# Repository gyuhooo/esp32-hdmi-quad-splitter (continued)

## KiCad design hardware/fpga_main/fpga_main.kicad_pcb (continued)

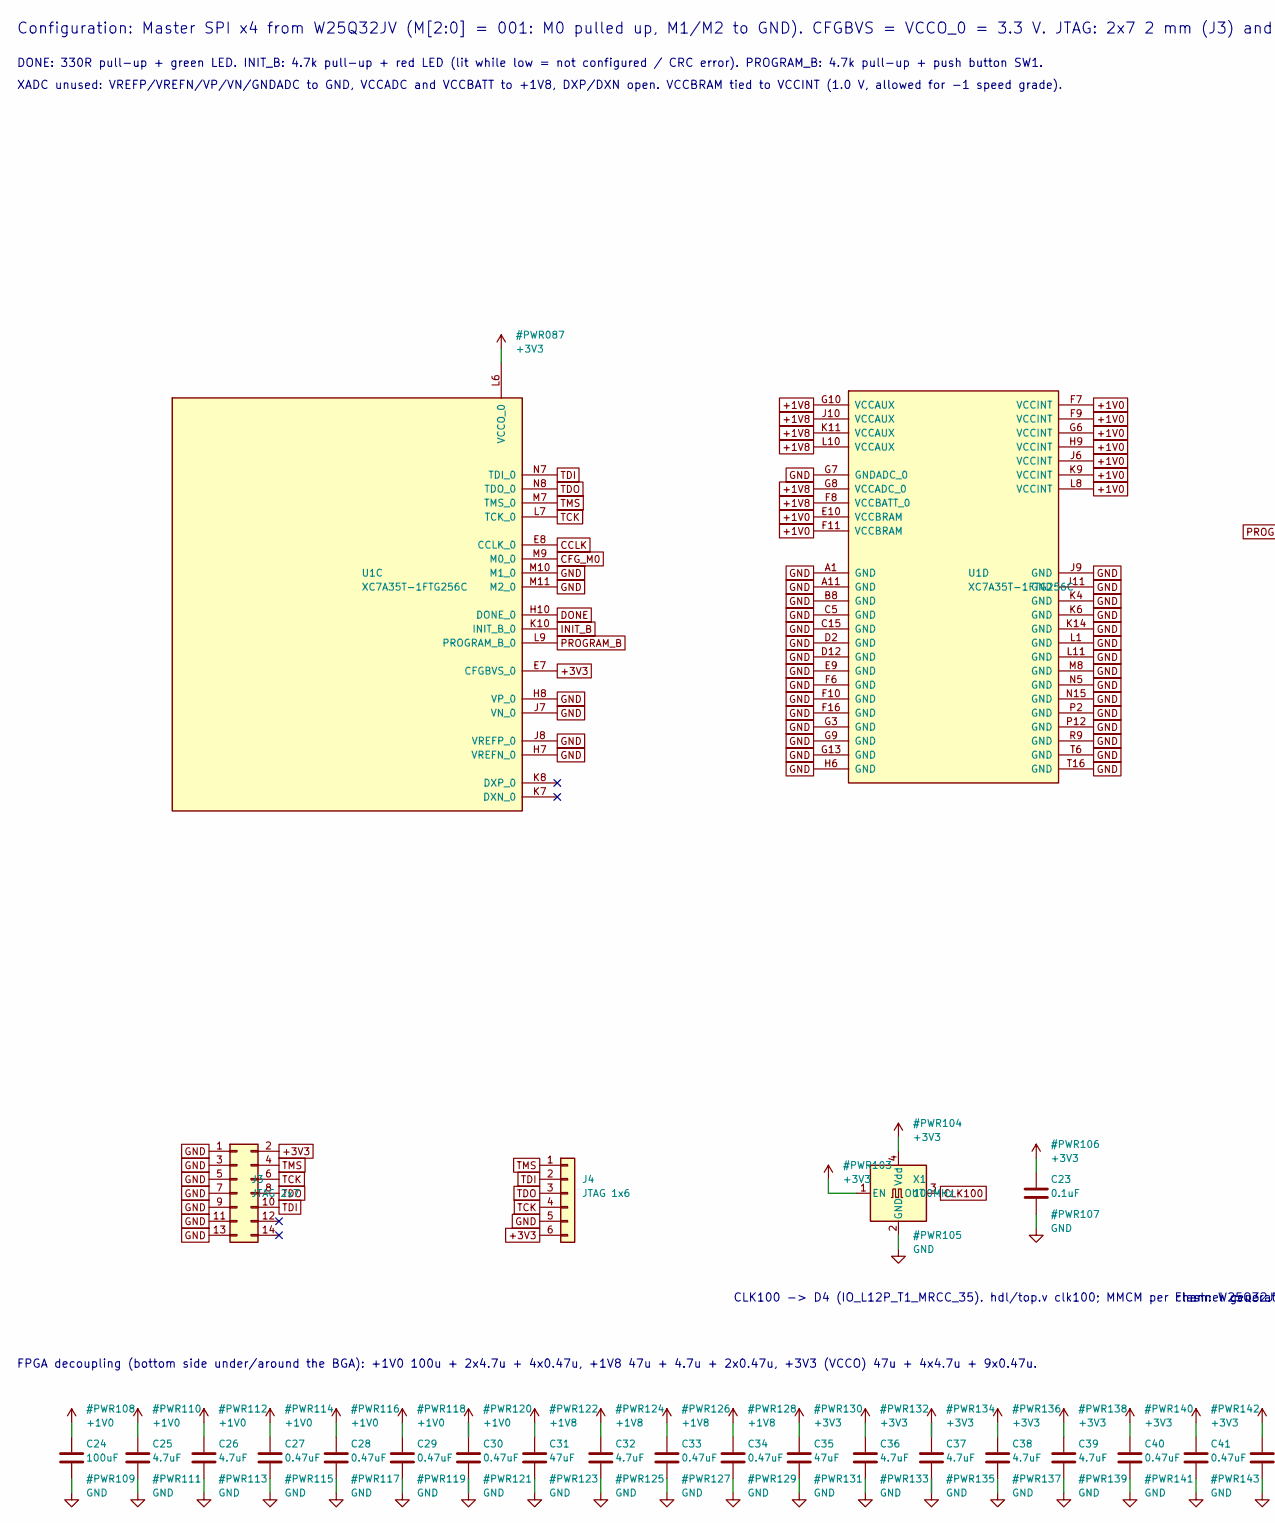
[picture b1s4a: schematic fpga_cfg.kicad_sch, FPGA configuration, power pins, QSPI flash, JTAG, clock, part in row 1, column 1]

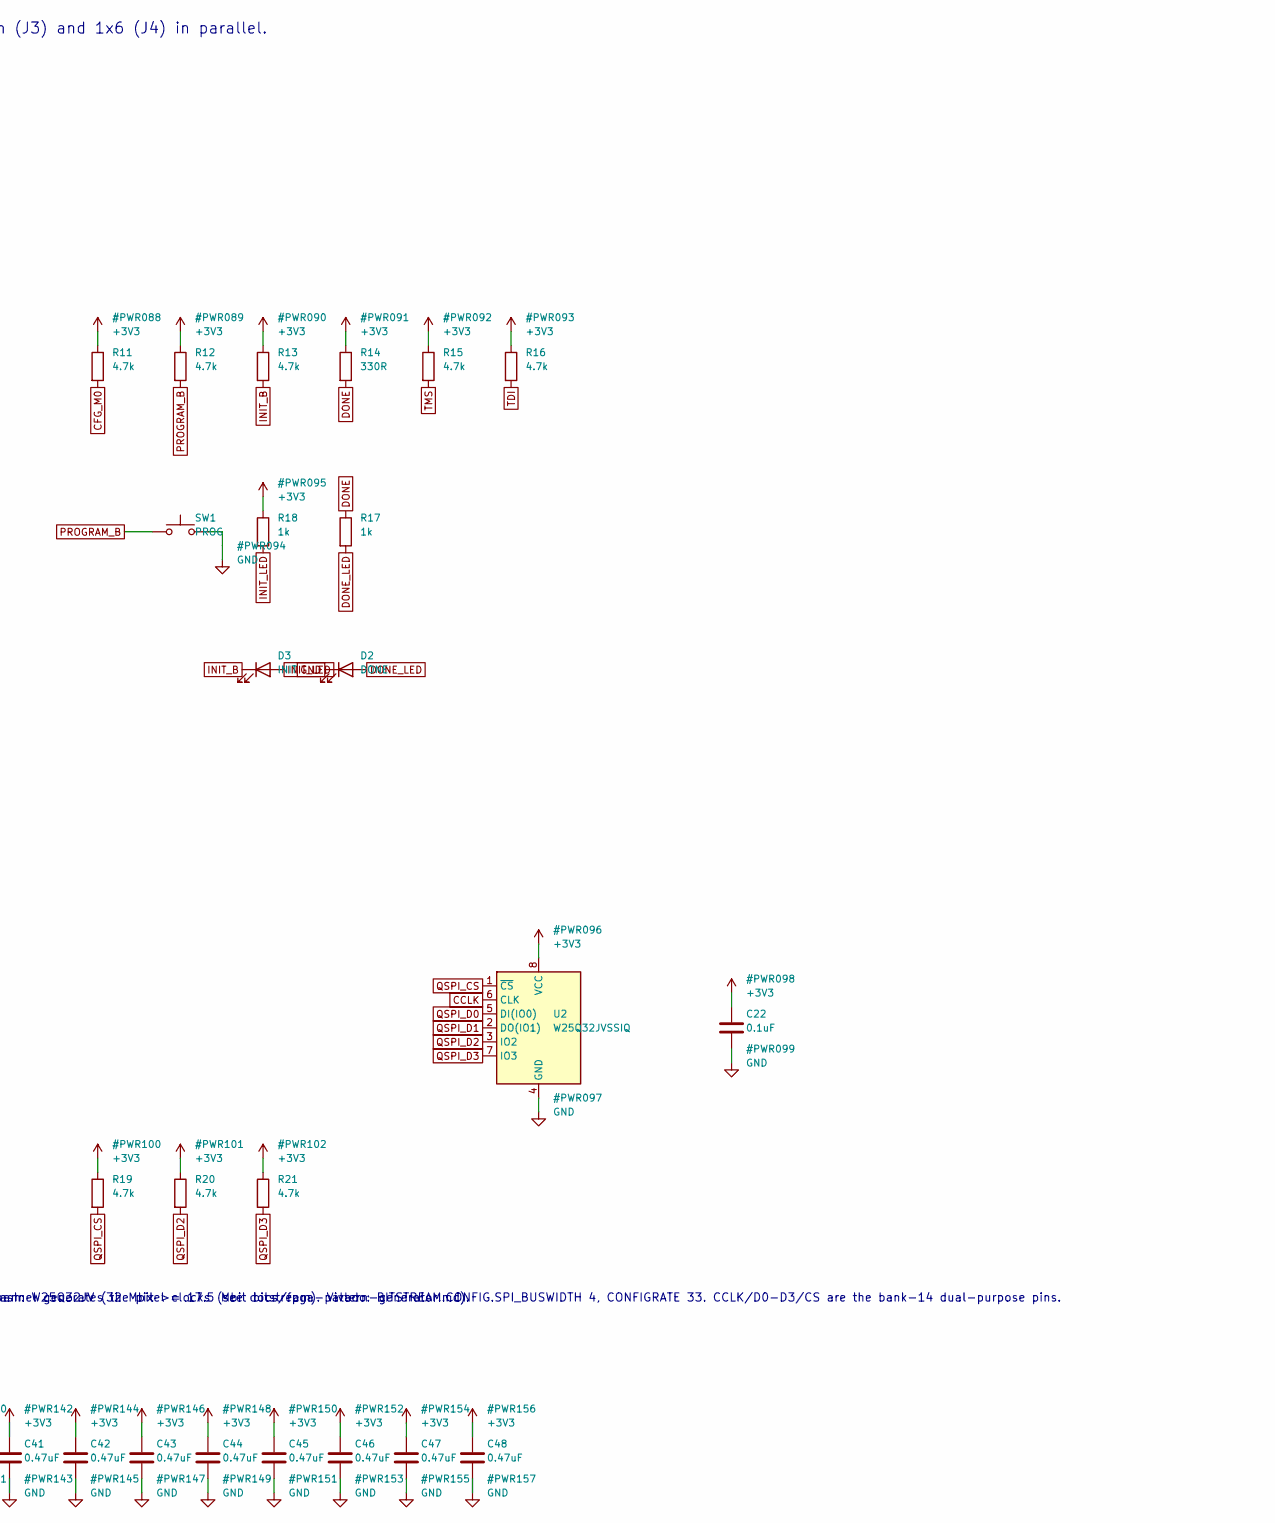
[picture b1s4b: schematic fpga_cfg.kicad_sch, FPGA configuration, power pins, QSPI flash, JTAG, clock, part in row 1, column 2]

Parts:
C22, C23: 0.1uF; C_0402_1005Metric; MPN GRM155R71C104KA88D
C24: 100uF; C_1206_3216Metric; MPN GRM31CR60J107ME39L
C25, C26, C32, C36, C37, C38, C39: 4.7uF; C_0603_1608Metric; MPN GRM188R60J475KE19D
C27, C28, C29, C30, C33, C34, C40, C41, C42, C43, C44, C45, C46, C47, C48: 0.47uF; C_0402_1005Metric; MPN GRM155R61A474KE15D
C31, C35: 47uF; C_0805_2012Metric; MPN GRM21BR60J476ME15L
D2: DONE; LED_0603_1608Metric; MPN LTST-C193KGKT-5A
D3: INIT; LED_0603_1608Metric; MPN LTST-C193KRKT-5A
J3: JTAG 2x7; PinHeader_2x07_P2.00mm_Vertical
J4: JTAG 1x6; PinHeader_1x06_P2.54mm_Vertical
R11, R12, R13, R15, R16, R19, R20, R21: 4.7k; R_0402_1005Metric; MPN RC0402FR-074K7L
R14: 330R; R_0402_1005Metric; MPN RC0402FR-07330RL
R17, R18: 1k; R_0402_1005Metric; MPN RC0402FR-071KL
SW1: PROG; SW_Push_1P1T_NO_CK_KMR2; MPN KMR221GLFS
U1: XC7A35T-1FTG256C; Xilinx_FTG256; MPN XC7A35T-1FTG256C
U2: W25Q32JVSSIQ; SOIC-8_5.23x5.23mm_P1.27mm; MPN W25Q32JVSSIQ
X1: 100MHz; Oscillator_SMD_Abracon_ASE-4Pin_3.2x2.5mm; MPN ASEM1-100.000MHZ-LC-T

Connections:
+1V0: C24.1, C25.1, C26.1, C27.1, C28.1, C29.1, C30.1, U1.E10 (VCCBRAM), U1.F7 (VCCINT), U1.F9 (VCCINT), U1.F11 (VCCBRAM), U1.G6 (VCCINT), U1.H9 (VCCINT), U1.J6 (VCCINT), U1.K9 (VCCINT), U1.L8 (VCCINT); also elsewhere on the board
+1V8: C31.1, C32.1, C33.1, C34.1, U1.F8 (VCCBATT_0), U1.G8 (VCCADC_0), U1.G10 (VCCAUX), U1.J10 (VCCAUX), U1.K11 (VCCAUX), U1.L10 (VCCAUX); also elsewhere on the board
+3V3: C22.1, C23.1, C35.1, C36.1, C37.1, C38.1, C39.1, C40.1, C41.1, C42.1, C43.1, C44.1, C45.1, C46.1, C47.1, C48.1, J3.2, J4.6, R11.1, R12.1, R13.1, R14.1, R15.1, R16.1, R18.1, R19.1, R20.1, R21.1, U1.E7 (CFGBVS_0), U1.L6 (VCCO_0), U2.8 (VCC), X1.1 (EN), X1.4 (Vdd); also elsewhere on the board
CCLK: U1.E8 (CCLK_0), U2.6 (CLK)
CFG_M0: R11.2, U1.M9 (M0_0)
CLK100: X1.3 (OUT); also elsewhere on the board
DONE: R14.2, R17.1, U1.H10 (DONE_0)
DONE_LED: D2.2 (A), R17.2
INIT_B: D3.1 (K), R13.2, U1.K10 (INIT_B_0)
INIT_LED: D3.2 (A), R18.2
PROGRAM_B: R12.2, SW1.1, U1.L9 (PROGRAM_B_0)
QSPI_CS: R19.2, U2.1 (~CS); also elsewhere on the board
QSPI_D0: U2.5 (DI(IO0)); also elsewhere on the board
QSPI_D1: U2.2 (DO(IO1)); also elsewhere on the board
QSPI_D2: R20.2, U2.3 (IO2); also elsewhere on the board
QSPI_D3: R21.2, U2.7 (IO3); also elsewhere on the board
TCK: J3.6, J4.4, U1.L7 (TCK_0)
TDI: J3.10, J4.2, R16.2, U1.N7 (TDI_0)
TDO: J3.8, J4.3, U1.N8 (TDO_0)
TMS: J3.4, J4.1, R15.2, U1.M7 (TMS_0)

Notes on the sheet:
Configuration: Master SPI x4 from W25Q32JV (M[2:0] = 001: M0 pulled up, M1/M2 to GND). CFGBVS = VCCO_0 = 3.3 V. JTAG: 2x7 2 mm (J3) and 1x6 (J4) in parallel.
DONE: 330R pull-up + green LED. INIT_B: 4.7k pull-up + red LED (lit while low = not configured / CRC error). PROGRAM_B: 4.7k pull-up + push button SW1.
XADC unused: VREFP/VREFN/VP/VN/GNDADC to GND, VCCADC and VCCBATT to +1V8, DXP/DXN open. VCCBRAM tied to VCCINT (1.0 V, allowed for -1 speed grade).
Flash: W25Q32JV (32 Mbit >= 17.5 Mbit bitstream). Vivado: BITSTREAM.CONFIG.SPI_BUSWIDTH 4, CONFIGRATE 33. CCLK/D0-D3/CS are the bank-14 dual-purpose pins.
CLK100 -> D4 (IO_L12P_T1_MRCC_35). hdl/top.v clk100; MMCM per channel generates the pixel clocks (see docs/fpga-pattern-generator.md).
FPGA decoupling (bottom side under/around the BGA): +1V0 100u + 2x4.7u + 4x0.47u, +1V8 47u + 4.7u + 2x0.47u, +3V3 (VCCO) 47u + 4x4.7u + 9x0.47u.

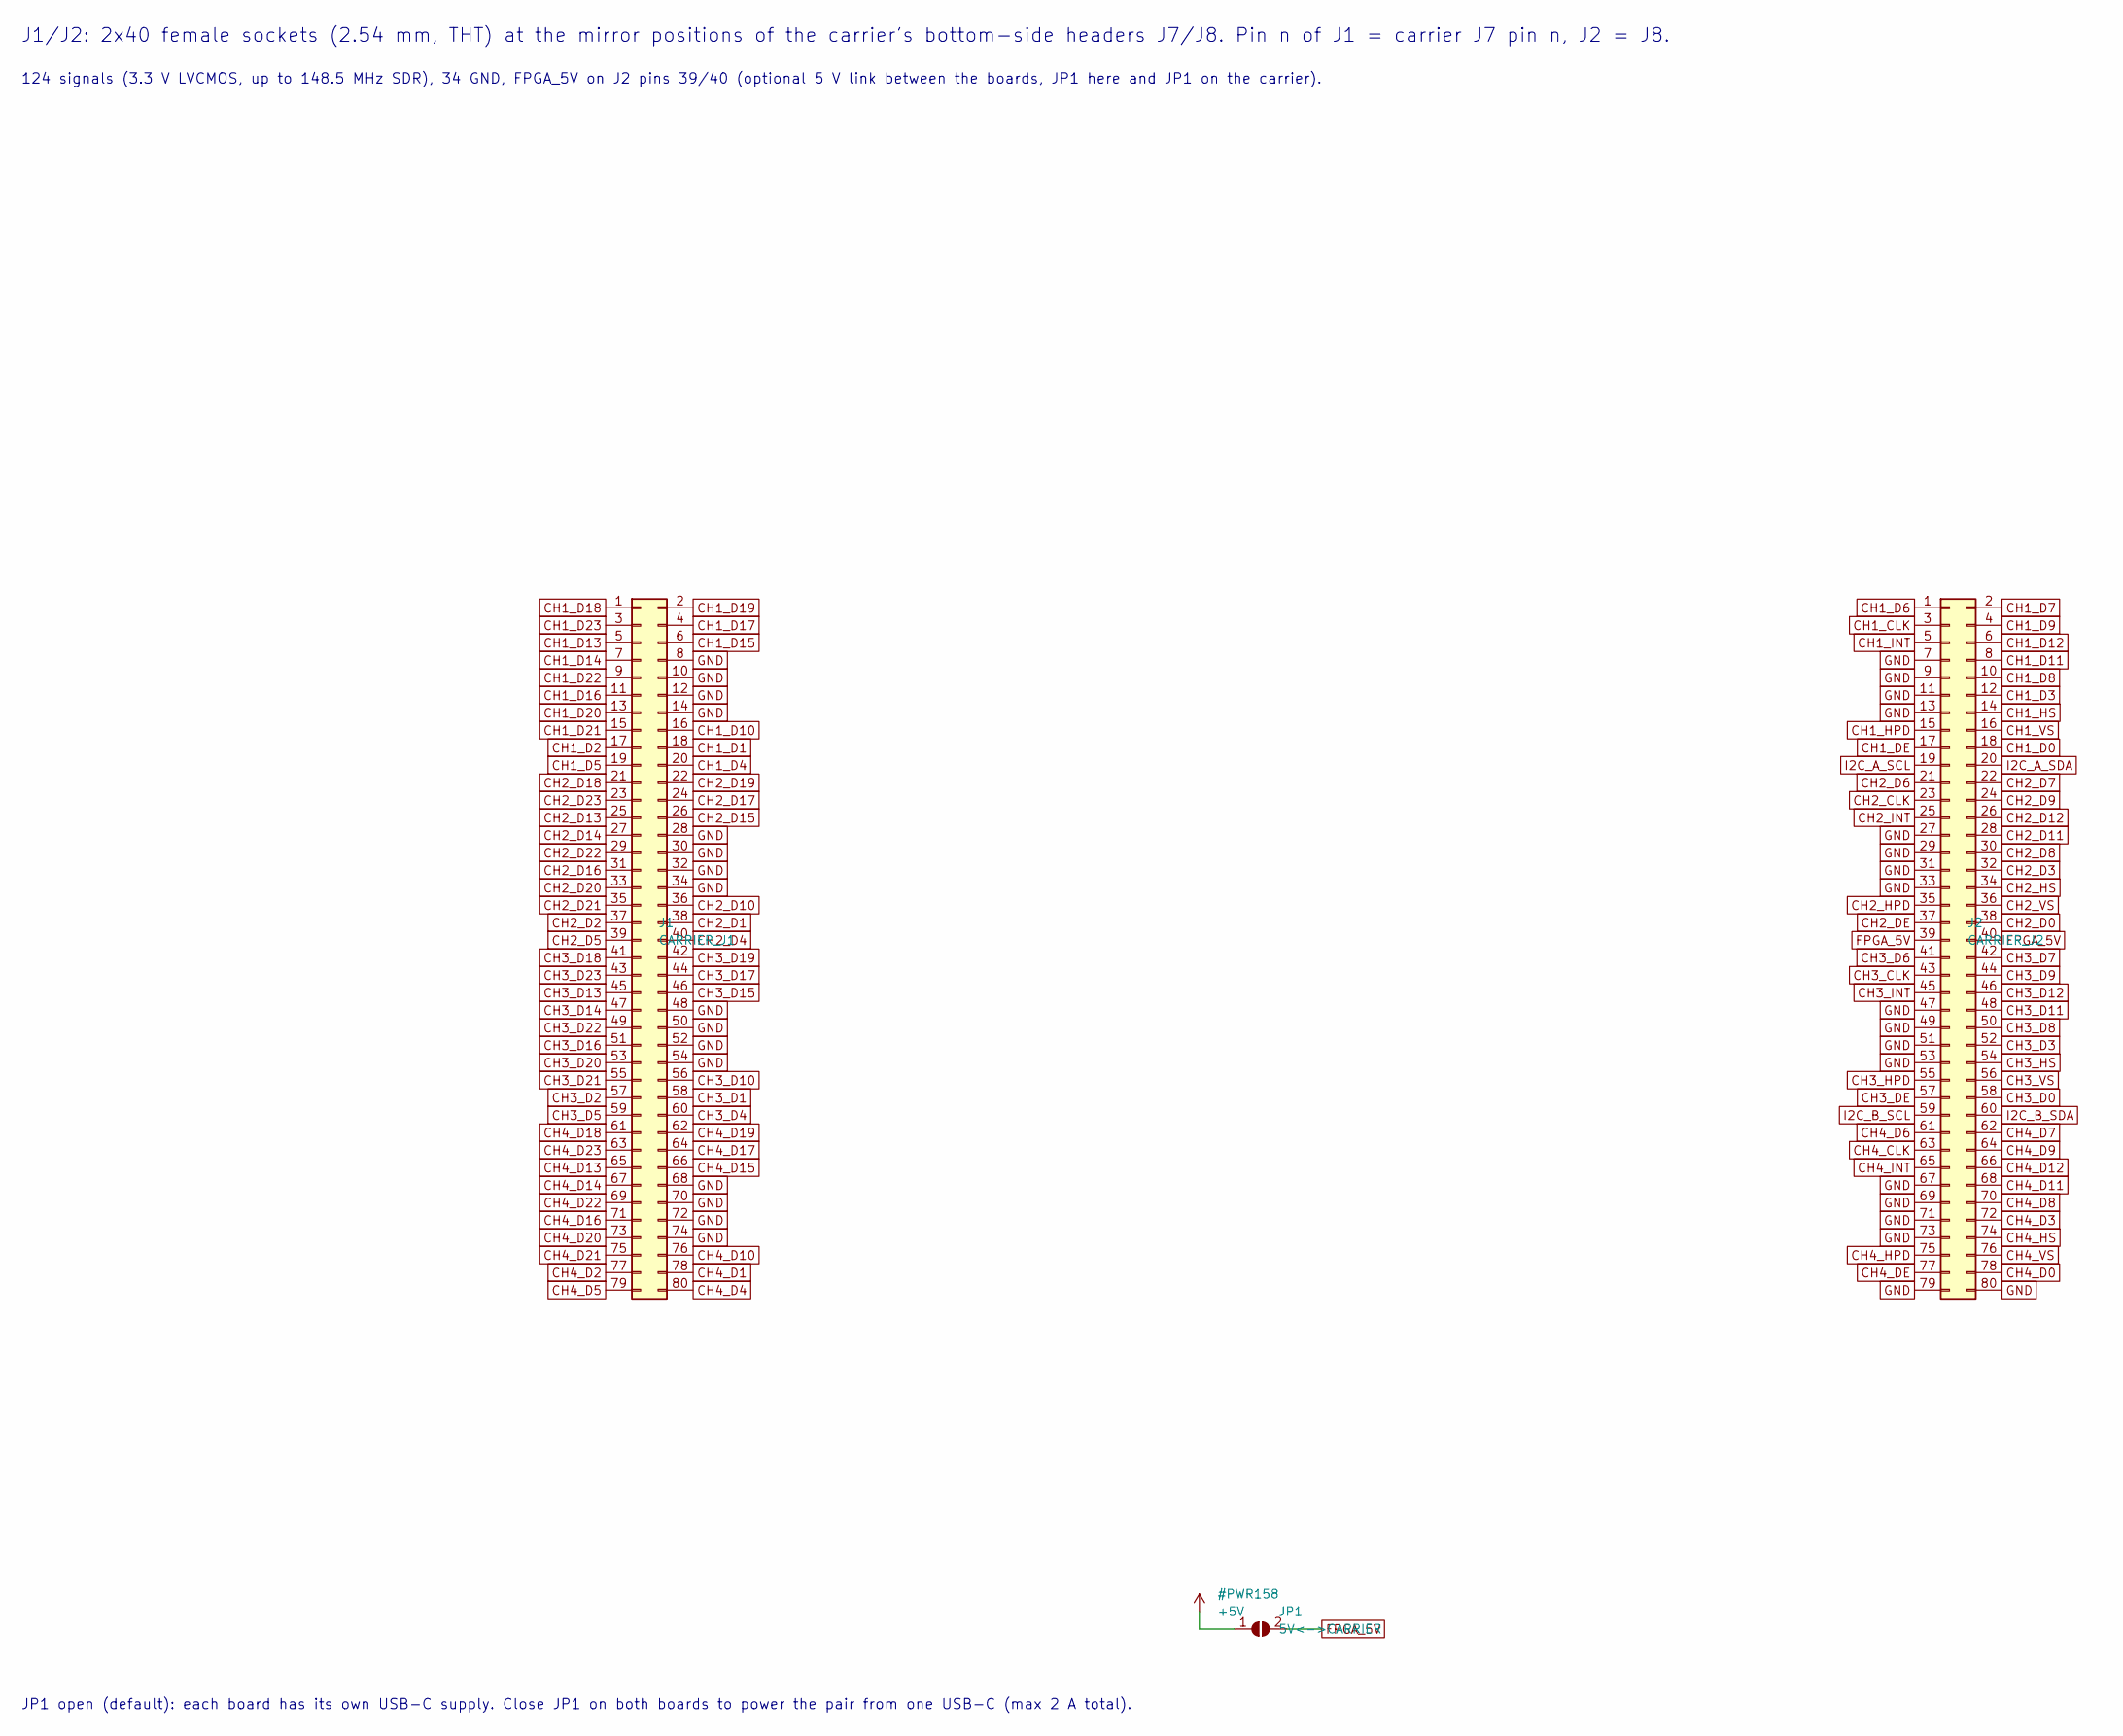
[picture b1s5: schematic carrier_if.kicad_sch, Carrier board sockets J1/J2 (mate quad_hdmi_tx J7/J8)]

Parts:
J1: CARRIER_J1; PinSocket_2x40_P2.54mm_Vertical; MPN PPTC402LFBN-RC
J2: CARRIER_J2; PinSocket_2x40_P2.54mm_Vertical; MPN PPTC402LFBN-RC
JP1: 5V<->CARRIER; SolderJumper-2_P1.3mm_Open_RoundedPad1.0x1.5mm

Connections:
+5V: JP1.1 (A); also elsewhere on the board
CH1_CLK: J2.3; also elsewhere on the board
CH1_D0: J2.18; also elsewhere on the board
CH1_D1: J1.18; also elsewhere on the board
CH1_D2: J1.17; also elsewhere on the board
CH1_D3: J2.12; also elsewhere on the board
CH1_D4: J1.20; also elsewhere on the board
CH1_D5: J1.19; also elsewhere on the board
CH1_D6: J2.1; also elsewhere on the board
CH1_D7: J2.2; also elsewhere on the board
CH1_D8: J2.10; also elsewhere on the board
CH1_D9: J2.4; also elsewhere on the board
CH1_D10: J1.16; also elsewhere on the board
CH1_D11: J2.8; also elsewhere on the board
CH1_D12: J2.6; also elsewhere on the board
CH1_D13: J1.5; also elsewhere on the board
CH1_D14: J1.7; also elsewhere on the board
CH1_D15: J1.6; also elsewhere on the board
CH1_D16: J1.11; also elsewhere on the board
CH1_D17: J1.4; also elsewhere on the board
CH1_D18: J1.1; also elsewhere on the board
CH1_D19: J1.2; also elsewhere on the board
CH1_D20: J1.13; also elsewhere on the board
CH1_D21: J1.15; also elsewhere on the board
CH1_D22: J1.9; also elsewhere on the board
CH1_D23: J1.3; also elsewhere on the board
CH1_DE: J2.17; also elsewhere on the board
CH1_HPD: J2.15; also elsewhere on the board
CH1_HS: J2.14; also elsewhere on the board
CH1_INT: J2.5; also elsewhere on the board
CH1_VS: J2.16; also elsewhere on the board
CH2_CLK: J2.23; also elsewhere on the board
CH2_D0: J2.38; also elsewhere on the board
CH2_D1: J1.38; also elsewhere on the board
CH2_D2: J1.37; also elsewhere on the board
CH2_D3: J2.32; also elsewhere on the board
CH2_D4: J1.40; also elsewhere on the board
CH2_D5: J1.39; also elsewhere on the board
CH2_D6: J2.21; also elsewhere on the board
CH2_D7: J2.22; also elsewhere on the board
CH2_D8: J2.30; also elsewhere on the board
CH2_D9: J2.24; also elsewhere on the board
CH2_D10: J1.36; also elsewhere on the board
CH2_D11: J2.28; also elsewhere on the board
CH2_D12: J2.26; also elsewhere on the board
CH2_D13: J1.25; also elsewhere on the board
CH2_D14: J1.27; also elsewhere on the board
CH2_D15: J1.26; also elsewhere on the board
CH2_D16: J1.31; also elsewhere on the board
CH2_D17: J1.24; also elsewhere on the board
CH2_D18: J1.21; also elsewhere on the board
CH2_D19: J1.22; also elsewhere on the board
CH2_D20: J1.33; also elsewhere on the board
CH2_D21: J1.35; also elsewhere on the board
CH2_D22: J1.29; also elsewhere on the board
CH2_D23: J1.23; also elsewhere on the board
CH2_DE: J2.37; also elsewhere on the board
CH2_HPD: J2.35; also elsewhere on the board
CH2_HS: J2.34; also elsewhere on the board
CH2_INT: J2.25; also elsewhere on the board
CH2_VS: J2.36; also elsewhere on the board
CH3_CLK: J2.43; also elsewhere on the board
CH3_D0: J2.58; also elsewhere on the board
CH3_D1: J1.58; also elsewhere on the board
CH3_D2: J1.57; also elsewhere on the board
CH3_D3: J2.52; also elsewhere on the board
CH3_D4: J1.60; also elsewhere on the board
CH3_D5: J1.59; also elsewhere on the board
CH3_D6: J2.41; also elsewhere on the board
CH3_D7: J2.42; also elsewhere on the board
CH3_D8: J2.50; also elsewhere on the board
CH3_D9: J2.44; also elsewhere on the board
CH3_D10: J1.56; also elsewhere on the board
CH3_D11: J2.48; also elsewhere on the board
CH3_D12: J2.46; also elsewhere on the board
CH3_D13: J1.45; also elsewhere on the board
CH3_D14: J1.47; also elsewhere on the board
CH3_D15: J1.46; also elsewhere on the board
CH3_D16: J1.51; also elsewhere on the board
CH3_D17: J1.44; also elsewhere on the board
CH3_D18: J1.41; also elsewhere on the board
CH3_D19: J1.42; also elsewhere on the board
CH3_D20: J1.53; also elsewhere on the board
CH3_D21: J1.55; also elsewhere on the board
CH3_D22: J1.49; also elsewhere on the board
CH3_D23: J1.43; also elsewhere on the board
CH3_DE: J2.57; also elsewhere on the board
CH3_HPD: J2.55; also elsewhere on the board
CH3_HS: J2.54; also elsewhere on the board
CH3_INT: J2.45; also elsewhere on the board
CH3_VS: J2.56; also elsewhere on the board
CH4_CLK: J2.63; also elsewhere on the board
CH4_D0: J2.78; also elsewhere on the board
CH4_D1: J1.78; also elsewhere on the board
CH4_D2: J1.77; also elsewhere on the board
CH4_D3: J2.72; also elsewhere on the board
CH4_D4: J1.80; also elsewhere on the board
CH4_D5: J1.79; also elsewhere on the board
CH4_D6: J2.61; also elsewhere on the board
CH4_D7: J2.62; also elsewhere on the board
CH4_D8: J2.70; also elsewhere on the board
CH4_D9: J2.64; also elsewhere on the board
CH4_D10: J1.76; also elsewhere on the board
CH4_D11: J2.68; also elsewhere on the board
CH4_D12: J2.66; also elsewhere on the board
CH4_D13: J1.65; also elsewhere on the board
CH4_D14: J1.67; also elsewhere on the board
CH4_D15: J1.66; also elsewhere on the board
CH4_D16: J1.71; also elsewhere on the board
CH4_D17: J1.64; also elsewhere on the board
CH4_D18: J1.61; also elsewhere on the board
CH4_D19: J1.62; also elsewhere on the board
CH4_D20: J1.73; also elsewhere on the board
CH4_D21: J1.75; also elsewhere on the board
CH4_D22: J1.69; also elsewhere on the board
CH4_D23: J1.63; also elsewhere on the board
CH4_DE: J2.77; also elsewhere on the board
CH4_HPD: J2.75; also elsewhere on the board
CH4_HS: J2.74; also elsewhere on the board
CH4_INT: J2.65; also elsewhere on the board
CH4_VS: J2.76; also elsewhere on the board
FPGA_5V: J2.39, J2.40, JP1.2 (B)
I2C_A_SCL: J2.19; also elsewhere on the board
I2C_A_SDA: J2.20; also elsewhere on the board
I2C_B_SCL: J2.59; also elsewhere on the board
I2C_B_SDA: J2.60; also elsewhere on the board

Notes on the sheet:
J1/J2: 2x40 female sockets (2.54 mm, THT) at the mirror positions of the carrier's bottom-side headers J7/J8. Pin n of J1 = carrier J7 pin n, J2 = J8.
124 signals (3.3 V LVCMOS, up to 148.5 MHz SDR), 34 GND, FPGA_5V on J2 pins 39/40 (optional 5 V link between the boards, JP1 here and JP1 on the carrier).
JP1 open (default): each board has its own USB-C supply. Close JP1 on both boards to power the pair from one USB-C (max 2 A total).

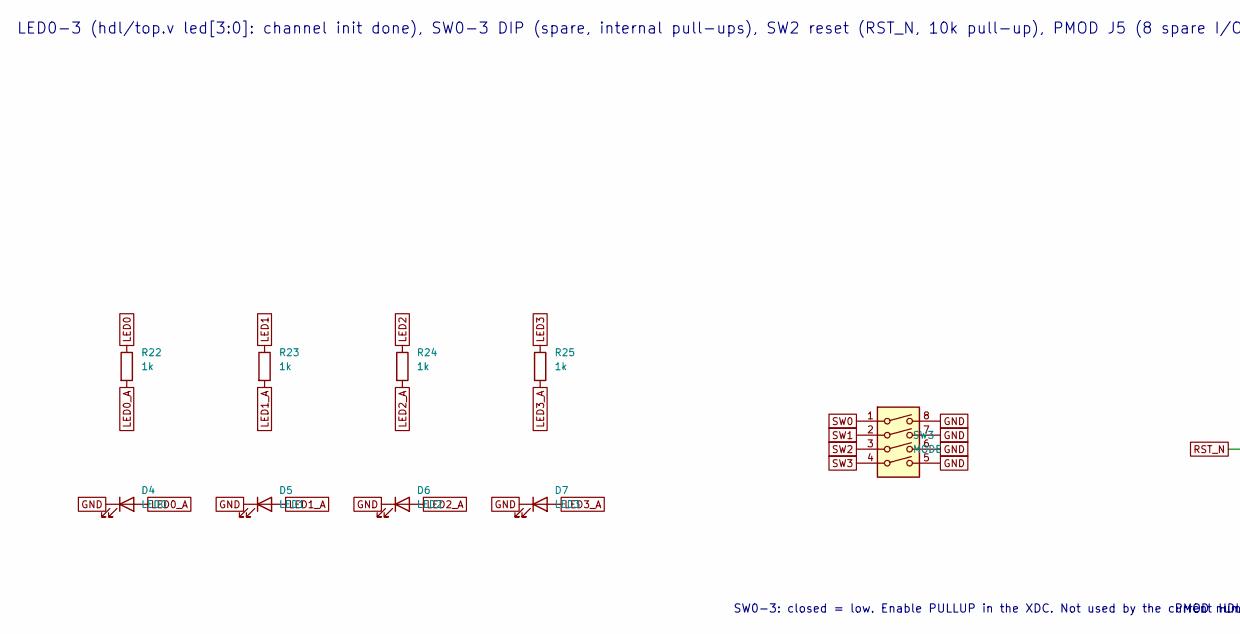
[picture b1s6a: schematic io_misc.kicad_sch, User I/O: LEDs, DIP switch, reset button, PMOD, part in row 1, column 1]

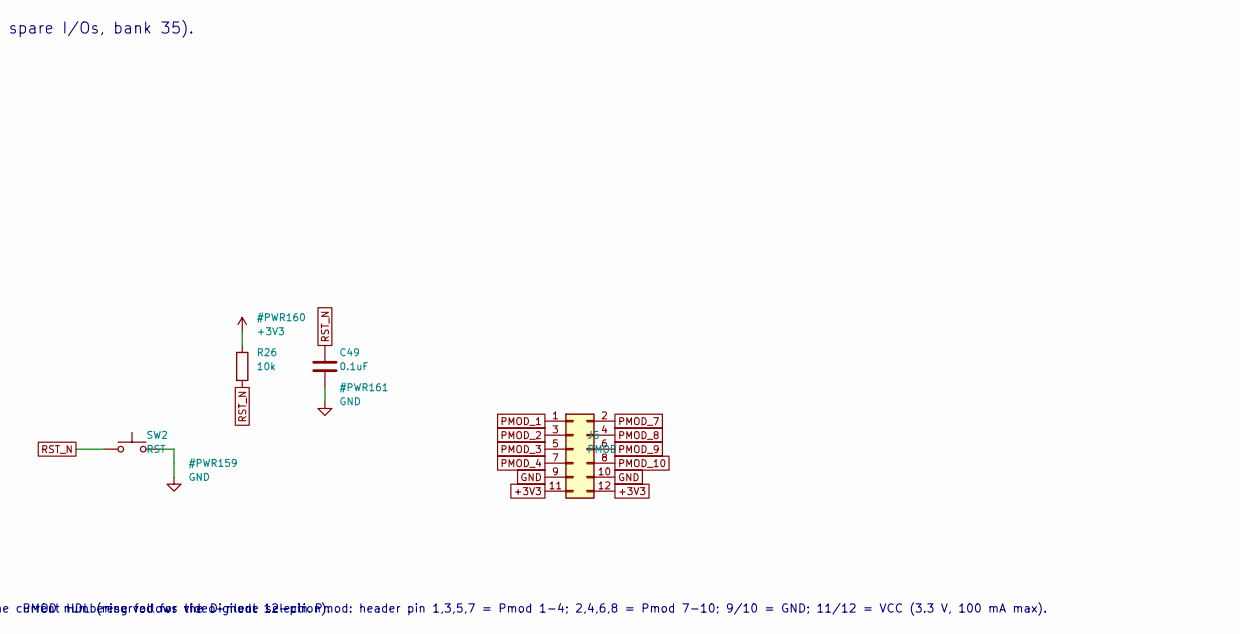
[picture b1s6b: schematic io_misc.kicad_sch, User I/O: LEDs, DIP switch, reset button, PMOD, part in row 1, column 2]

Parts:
C49: 0.1uF; C_0402_1005Metric; MPN GRM155R71C104KA88D
D4: LED0; LED_0603_1608Metric; MPN LTST-C193KGKT-5A
D5: LED1; LED_0603_1608Metric; MPN LTST-C193KGKT-5A
D6: LED2; LED_0603_1608Metric; MPN LTST-C193KGKT-5A
D7: LED3; LED_0603_1608Metric; MPN LTST-C193KGKT-5A
J5: PMOD; PinHeader_2x06_P2.54mm_Vertical
R22, R23, R24, R25: 1k; R_0402_1005Metric; MPN RC0402FR-071KL
R26: 10k; R_0402_1005Metric; MPN RC0402FR-0710KL
SW2: RST; SW_Push_1P1T_NO_CK_KMR2; MPN KMR221GLFS
SW3: MODE; SW_DIP_SPSTx04_Slide_Copal_CHS-04B_W7.62mm_P1.27mm; MPN CHS-04B

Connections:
+3V3: J5.11, J5.12, R26.1; also elsewhere on the board
LED0: R22.1; also elsewhere on the board
LED0_A: D4.2 (A), R22.2
LED1: R23.1; also elsewhere on the board
LED1_A: D5.2 (A), R23.2
LED2: R24.1; also elsewhere on the board
LED2_A: D6.2 (A), R24.2
LED3: R25.1; also elsewhere on the board
LED3_A: D7.2 (A), R25.2
PMOD_1: J5.1; also elsewhere on the board
PMOD_2: J5.3; also elsewhere on the board
PMOD_3: J5.5; also elsewhere on the board
PMOD_4: J5.7; also elsewhere on the board
PMOD_7: J5.2; also elsewhere on the board
PMOD_8: J5.4; also elsewhere on the board
PMOD_9: J5.6; also elsewhere on the board
PMOD_10: J5.8; also elsewhere on the board
RST_N: C49.1, R26.2, SW2.1; also elsewhere on the board
SW0: SW3.1; also elsewhere on the board
SW1: SW3.2; also elsewhere on the board
SW2: SW3.3; also elsewhere on the board
SW3: SW3.4; also elsewhere on the board

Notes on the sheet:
LED0-3 (hdl/top.v led[3:0]: channel init done), SW0-3 DIP (spare, internal pull-ups), SW2 reset (RST_N, 10k pull-up), PMOD J5 (8 spare I/Os, bank 35).
SW0-3: closed = low. Enable PULLUP in the XDC. Not used by the current HDL (reserved for video-mode selection).
PMOD numbering follows the Digilent 12-pin Pmod: header pin 1,3,5,7 = Pmod 1-4; 2,4,6,8 = Pmod 7-10; 9/10 = GND; 11/12 = VCC (3.3 V, 100 mA max).

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
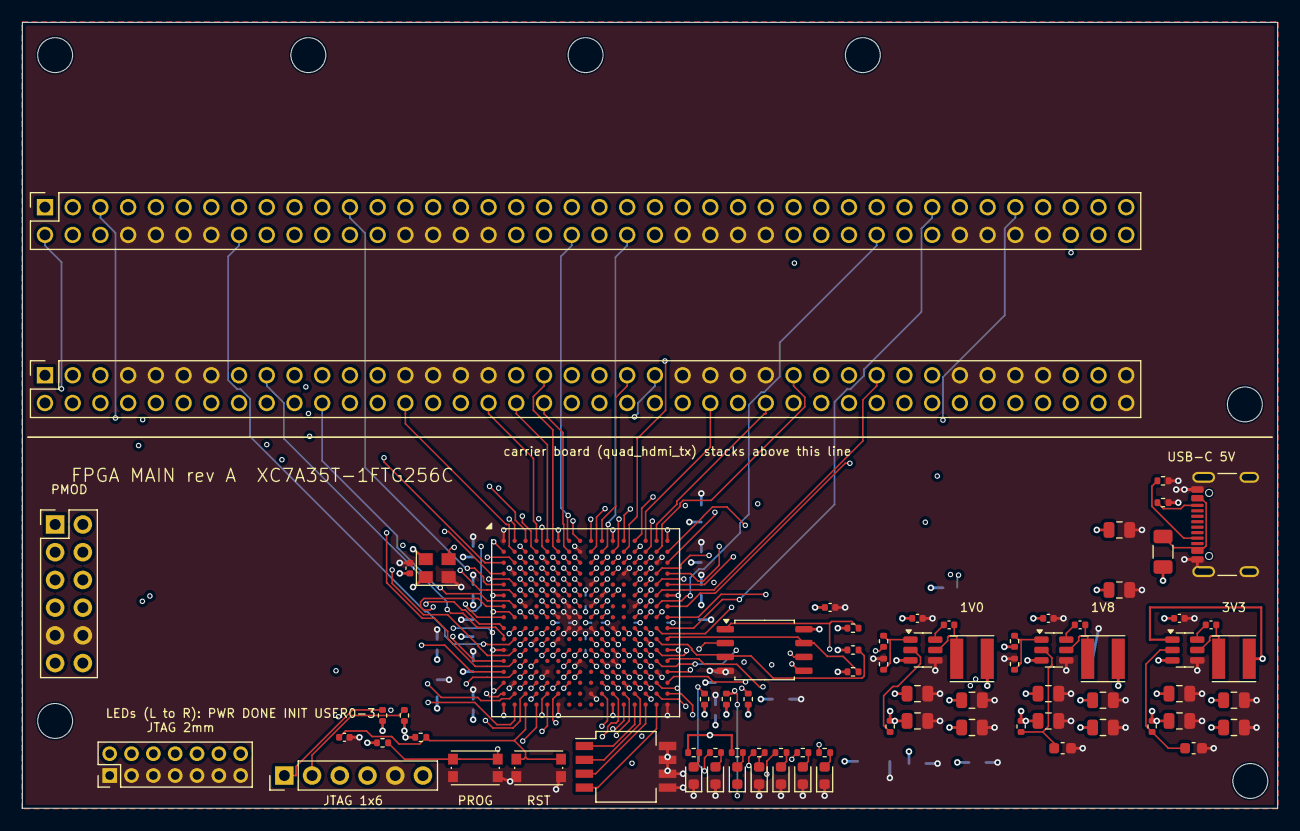
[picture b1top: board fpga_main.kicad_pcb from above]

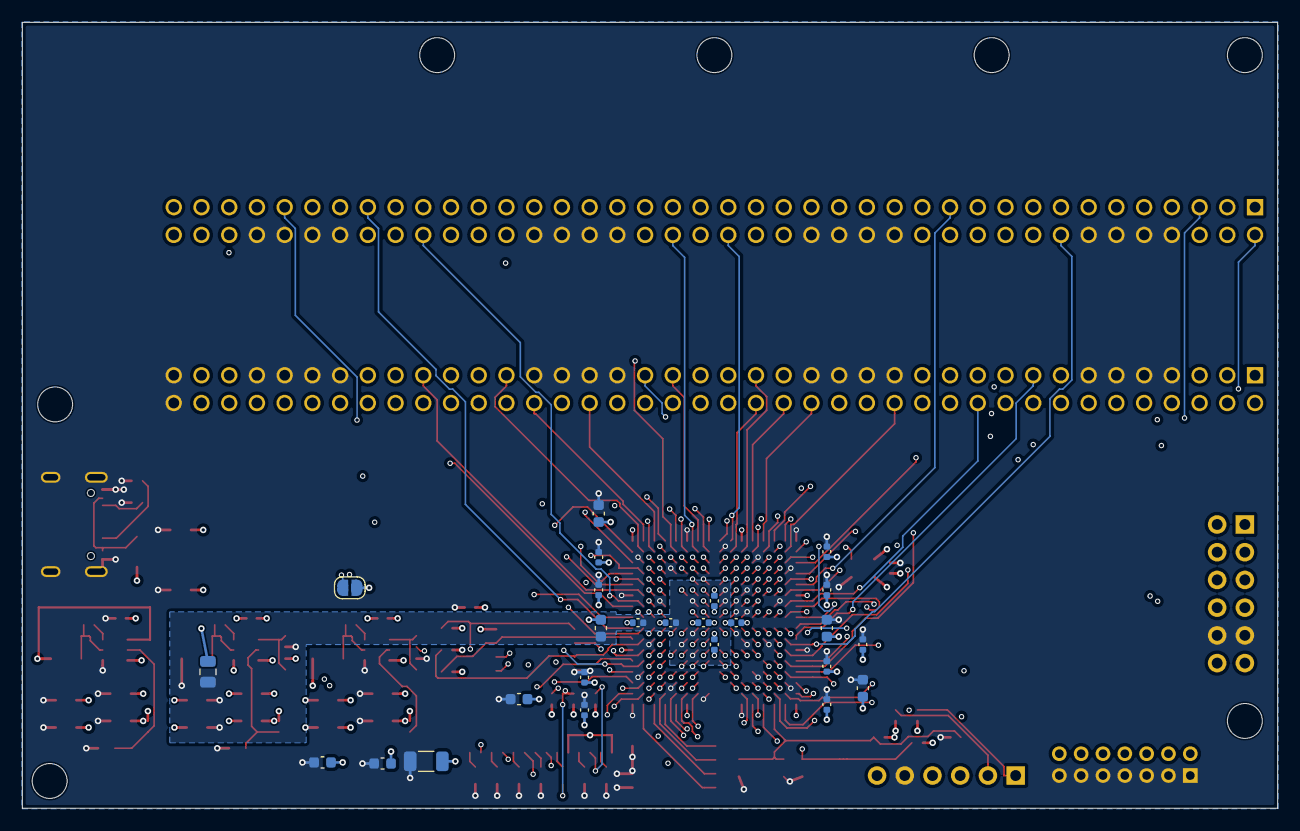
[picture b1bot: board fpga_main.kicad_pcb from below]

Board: 6 copper layers, 115.0 x 72.0 mm, 109 parts (25 on the bottom side), 183 nets.

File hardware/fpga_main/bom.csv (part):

Reference,Value,Footprint,MPN,Description
C1,22uF,Capacitor_SMD:C_0805_2012Metric,GRM21BR60J226ME39L,22uF 6.3V X5R 0805
C2,0.1uF,Capacitor_SMD:C_0402_1005Metric,GRM155R71C104KA88D,0.1uF 16V X7R 0402
C3,10uF,Capacitor_SMD:C_0805_2012Metric,GRM21BR61A106KE19L,10uF 10V X5R 0805
C4,10uF,Capacitor_SMD:C_0805_2012Metric,GRM21BR61A106KE19L,10uF 10V X5R 0805
C5,0.1uF,Capacitor_SMD:C_0402_1005Metric,GRM155R71C104KA88D,0.1uF 16V X7R 0402
C6,22uF,Capacitor_SMD:C_0805_2012Metric,GRM21BR60J226ME39L,22uF 6.3V X5R 0805
C7,22uF,Capacitor_SMD:C_0805_2012Metric,GRM21BR60J226ME39L,22uF 6.3V X5R 0805
C8,0.1uF,Capacitor_SMD:C_0402_1005Metric,GRM155R71C104KA88D,0.1uF 16V X7R 0402
C9,10uF,Capacitor_SMD:C_0805_2012Metric,GRM21BR61A106KE19L,10uF 10V X5R 0805
C10,10uF,Capacitor_SMD:C_0805_2012Metric,GRM21BR61A106KE19L,10uF 10V X5R 0805
C11,0.1uF,Capacitor_SMD:C_0402_1005Metric,GRM155R71C104KA88D,0.1uF 16V X7R 0402
C12,22uF,Capacitor_SMD:C_0805_2012Metric,GRM21BR60J226ME39L,22uF 6.3V X5R 0805
C13,22uF,Capacitor_SMD:C_0805_2012Metric,GRM21BR60J226ME39L,22uF 6.3V X5R 0805
C14,1uF,Capacitor_SMD:C_0603_1608Metric,GRM188R61A105KA61D,1uF 0603 (EN delay)
C15,0.1uF,Capacitor_SMD:C_0402_1005Metric,GRM155R71C104KA88D,0.1uF 16V X7R 0402
C16,10uF,Capacitor_SMD:C_0805_2012Metric,GRM21BR61A106KE19L,10uF 10V X5R 0805
C17,10uF,Capacitor_SMD:C_0805_2012Metric,GRM21BR61A106KE19L,10uF 10V X5R 0805
C18,0.1uF,Capacitor_SMD:C_0402_1005Metric,GRM155R71C104KA88D,0.1uF 16V X7R 0402
C19,22uF,Capacitor_SMD:C_0805_2012Metric,GRM21BR60J226ME39L,22uF 6.3V X5R 0805
C20,22uF,Capacitor_SMD:C_0805_2012Metric,GRM21BR60J226ME39L,22uF 6.3V X5R 0805
C21,2.2uF,Capacitor_SMD:C_0603_1608Metric,GRM188R61A225KE34D,2.2uF 0603 (EN delay)
C22,0.1uF,Capacitor_SMD:C_0402_1005Metric,GRM155R71C104KA88D,0.1uF 16V X7R 0402
C23,0.1uF,Capacitor_SMD:C_0402_1005Metric,GRM155R71C104KA88D,0.1uF 16V X7R 0402
C24,100uF,Capacitor_SMD:C_1206_3216Metric,GRM31CR60J107ME39L,100uF 6.3V X5R 1206
C25,4.7uF,Capacitor_SMD:C_0603_1608Metric,GRM188R60J475KE19D,4.7uF 6.3V X5R 0603
C26,4.7uF,Capacitor_SMD:C_0603_1608Metric,GRM188R60J475KE19D,4.7uF 6.3V X5R 0603
C27,0.47uF,Capacitor_SMD:C_0402_1005Metric,GRM155R61A474KE15D,0.47uF 10V X5R 0402
C28,0.47uF,Capacitor_SMD:C_0402_1005Metric,GRM155R61A474KE15D,0.47uF 10V X5R 0402
C29,0.47uF,Capacitor_SMD:C_0402_1005Metric,GRM155R61A474KE15D,0.47uF 10V X5R 0402
C30,0.47uF,Capacitor_SMD:C_0402_1005Metric,GRM155R61A474KE15D,0.47uF 10V X5R 0402
C31,47uF,Capacitor_SMD:C_0805_2012Metric,GRM21BR60J476ME15L,47uF 6.3V X5R 0805
C32,4.7uF,Capacitor_SMD:C_0603_1608Metric,GRM188R60J475KE19D,4.7uF 6.3V X5R 0603
C33,0.47uF,Capacitor_SMD:C_0402_1005Metric,GRM155R61A474KE15D,0.47uF 10V X5R 0402
C34,0.47uF,Capacitor_SMD:C_0402_1005Metric,GRM155R61A474KE15D,0.47uF 10V X5R 0402
C35,47uF,Capacitor_SMD:C_0805_2012Metric,GRM21BR60J476ME15L,47uF 6.3V X5R 0805
C36,4.7uF,Capacitor_SMD:C_0603_1608Metric,GRM188R60J475KE19D,4.7uF 6.3V X5R 0603
C37,4.7uF,Capacitor_SMD:C_0603_1608Metric,GRM188R60J475KE19D,4.7uF 6.3V X5R 0603
C38,4.7uF,Capacitor_SMD:C_0603_1608Metric,GRM188R60J475KE19D,4.7uF 6.3V X5R 0603
C39,4.7uF,Capacitor_SMD:C_0603_1608Metric,GRM188R60J475KE19D,4.7uF 6.3V X5R 0603
C40,0.47uF,Capacitor_SMD:C_0402_1005Metric,GRM155R61A474KE15D,0.47uF 10V X5R 0402
C41,0.47uF,Capacitor_SMD:C_0402_1005Metric,GRM155R61A474KE15D,0.47uF 10V X5R 0402
C42,0.47uF,Capacitor_SMD:C_0402_1005Metric,GRM155R61A474KE15D,0.47uF 10V X5R 0402
C43,0.47uF,Capacitor_SMD:C_0402_1005Metric,GRM155R61A474KE15D,0.47uF 10V X5R 0402
C44,0.47uF,Capacitor_SMD:C_0402_1005Metric,GRM155R61A474KE15D,0.47uF 10V X5R 0402
C45,0.47uF,Capacitor_SMD:C_0402_1005Metric,GRM155R61A474KE15D,0.47uF 10V X5R 0402
C46,0.47uF,Capacitor_SMD:C_0402_1005Metric,GRM155R61A474KE15D,0.47uF 10V X5R 0402
C47,0.47uF,Capacitor_SMD:C_0402_1005Metric,GRM155R61A474KE15D,0.47uF 10V X5R 0402
C48,0.47uF,Capacitor_SMD:C_0402_1005Metric,GRM155R61A474KE15D,0.47uF 10V X5R 0402
C49,0.1uF,Capacitor_SMD:C_0402_1005Metric,GRM155R71C104KA88D,0.1uF 16V X7R 0402
D1,PWR,LED_SMD:LED_0603_1608Metric,LTST-C193KGKT-5A,Green LED 0603 (3.3 V power)
D2,DONE,LED_SMD:LED_0603_1608Metric,LTST-C193KGKT-5A,Green LED 0603 (DONE)
D3,INIT,LED_SMD:LED_0603_1608Metric,LTST-C193KRKT-5A,Red LED 0603 (INIT_B low)
D4,LED0,LED_SMD:LED_0603_1608Metric,LTST-C193KGKT-5A,Green LED 0603 (user LED0)
D5,LED1,LED_SMD:LED_0603_1608Metric,LTST-C193KGKT-5A,Green LED 0603 (user LED1)
D6,LED2,LED_SMD:LED_0603_1608Metric,LTST-C193KGKT-5A,Green LED 0603 (user LED2)
D7,LED3,LED_SMD:LED_0603_1608Metric,LTST-C193KGKT-5A,Green LED 0603 (user LED3)
F1,2A,Fuse:Fuse_1206_3216Metric,1206L200/12SLYR,"PTC resettable fuse 2 A hold, 1206"
H1,M3,MountingHole:MountingHole_3.2mm_M3,,Mounting hole M3
H2,M3,MountingHole:MountingHole_3.2mm_M3,,Mounting hole M3
H3,M3,MountingHole:MountingHole_3.2mm_M3,,Mounting hole M3
H4,M3,MountingHole:MountingHole_3.2mm_M3,,Mounting hole M3
H5,M3,MountingHole:MountingHole_3.2mm_M3,,Mounting hole M3
H6,M3,MountingHole:MountingHole_3.2mm_M3,,Mounting hole M3
H7,M3,MountingHole:MountingHole_3.2mm_M3,,Mounting hole M3
J1,CARRIER_J1,Connector_PinSocket_2.54mm:PinSocket_2x40_P2.54mm_Vertical,PPTC402LFBN-RC,"2x40 female socket 2.54 mm, 8.5 mm high (Sullins PPTC402LFBN-RC)"
J2,CARRIER_J2,Connector_PinSocket_2.54mm:PinSocket_2x40_P2.54mm_Vertical,PPTC402LFBN-RC,"2x40 female socket 2.54 mm, 8.5 mm high (Sullins PPTC402LFBN-RC)"
J3,JTAG 2x7,Connector_PinHeader_2.00mm:PinHeader_2x07_P2.00mm_Vertical,,"2x7 pin header 2.0 mm (Xilinx 14-pin JTAG cable: 2 VREF, 4 TMS, 6 TCK, 8 TDO, 10 TDI, odd = GND)"
J4,JTAG 1x6,Connector_PinHeader_2.54mm:PinHeader_1x06_P2.54mm_Vertical,,1x6 pin header 2.54 mm (Digilent JTAG-HS2/HS3 pinout: TMS TDI TDO TCK GND VREF)
J5,PMOD,Connector_PinHeader_2.54mm:PinHeader_2x06_P2.54mm_Vertical,,"2x6 pin header 2.54 mm (Digilent Pmod pinout: 1-4/7-10 I/O, 5/11 GND, 6/12 3.3 V)"
J10,USB-C 5V in,Connector_USB:USB_C_Receptacle_GCT_USB4105-xx-A_16P_TopMnt_Horizontal,USB4105-GF-A,USB-C receptacle 16P (power only)
JP1,5V<->CARRIER,Jumper:SolderJumper-2_P1.3mm_Open_RoundedPad1.0x1.5mm,,Solder jumper: link +5V with FPGA_5V (J2 pins 39/40)
L1,4.7uH,Inductor_SMD:L_Taiyo-Yuden_NR-40xx,NR4018T4R7M,4.7uH 2.2A shielded inductor 4x4 mm
L2,4.7uH,Inductor_SMD:L_Taiyo-Yuden_NR-40xx,NR4018T4R7M,4.7uH 2.2A shielded inductor 4x4 mm
L3,4.7uH,Inductor_SMD:L_Taiyo-Yuden_NR-40xx,NR4018T4R7M,4.7uH 2.2A shielded inductor 4x4 mm
R1,5.1k,Resistor_SMD:R_0402_1005Metric,RC0402FR-075K1L,5.1k 0402 (USB-C sink CC)
R2,5.1k,Resistor_SMD:R_0402_1005Metric,RC0402FR-075K1L,5.1k 0402 (USB-C sink CC)
R3,10k,Resistor_SMD:R_0402_1005Metric,RC0402FR-0710KL,10k 1% 0402 (FB top)
R4,40.2k,Resistor_SMD:R_0402_1005Metric,RC0402FR-0740K2L,40.2k 1% 0402 (FB bottom)
R5,100k,Resistor_SMD:R_0402_1005Metric,RC0402FR-07100KL,100k 0402 (EN pull-up)
R6,24.9k,Resistor_SMD:R_0402_1005Metric,RC0402FR-0724K9L,24.9k 1% 0402 (FB top)
R7,20k,Resistor_SMD:R_0402_1005Metric,RC0402FR-0720KL,20k 1% 0402 (FB bottom)
R8,100k,Resistor_SMD:R_0402_1005Metric,RC0402FR-07100KL,100k 0402 (EN pull-up)
R9,100k,Resistor_SMD:R_0402_1005Metric,RC0402FR-07100KL,100k 0402 (EN pull-up)
R10,1k,Resistor_SMD:R_0402_1005Metric,RC0402FR-071KL,1k 0402 (power LED)
R11,4.7k,Resistor_SMD:R_0402_1005Metric,RC0402FR-074K7L,4.7k 0402 (M0 pull-up: mode 001 master SPI)
R12,4.7k,Resistor_SMD:R_0402_1005Metric,RC0402FR-074K7L,4.7k 0402 (PROGRAM_B pull-up)
R13,4.7k,Resistor_SMD:R_0402_1005Metric,RC0402FR-074K7L,4.7k 0402 (INIT_B pull-up)
R14,330R,Resistor_SMD:R_0402_1005Metric,RC0402FR-07330RL,330R 0402 (DONE pull-up)
R15,4.7k,Resistor_SMD:R_0402_1005Metric,RC0402FR-074K7L,4.7k 0402 (TMS pull-up)
R16,4.7k,Resistor_SMD:R_0402_1005Metric,RC0402FR-074K7L,4.7k 0402 (TDI pull-up)
R17,1k,Resistor_SMD:R_0402_1005Metric,RC0402FR-071KL,1k 0402 (DONE LED)
R18,1k,Resistor_SMD:R_0402_1005Metric,RC0402FR-071KL,1k 0402 (INIT LED)
R19,4.7k,Resistor_SMD:R_0402_1005Metric,RC0402FR-074K7L,4.7k 0402 (flash CS pull-up)
R20,4.7k,Resistor_SMD:R_0402_1005Metric,RC0402FR-074K7L,4.7k 0402 (flash WP pull-up)
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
